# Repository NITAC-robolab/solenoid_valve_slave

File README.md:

# 概要
電磁弁を制御するためのスレーブ．

<br>
<br>

# リポジトリ構成
```tree
├── circuit --> 回路図，基板データ
└── program --> プログラム
```

<br>
<br>

# 動作確認環境
- IDE : MPLAB X IDE v4.15
- コンパイラ : XC16 v1.41
- コンパイルオプション : -std=c99
    - File -> Project Properties -> Categories: -> Conf: [default] -> XC16(Global Options) -> xc16-gcc -> Additional options: で指定

<br>
<br>

# 通信データ ( M->S )

| byte | 内容 |
|:-:|:--|
| 1 | ON / OFF ( 1ch ~ 8ch )|
| 2 | ON / OFF ( 9ch ~ 16ch )|

<br>
<br>

# 使用している周辺モジュール

* UART1(RX) ：Raspberry Pi との通信

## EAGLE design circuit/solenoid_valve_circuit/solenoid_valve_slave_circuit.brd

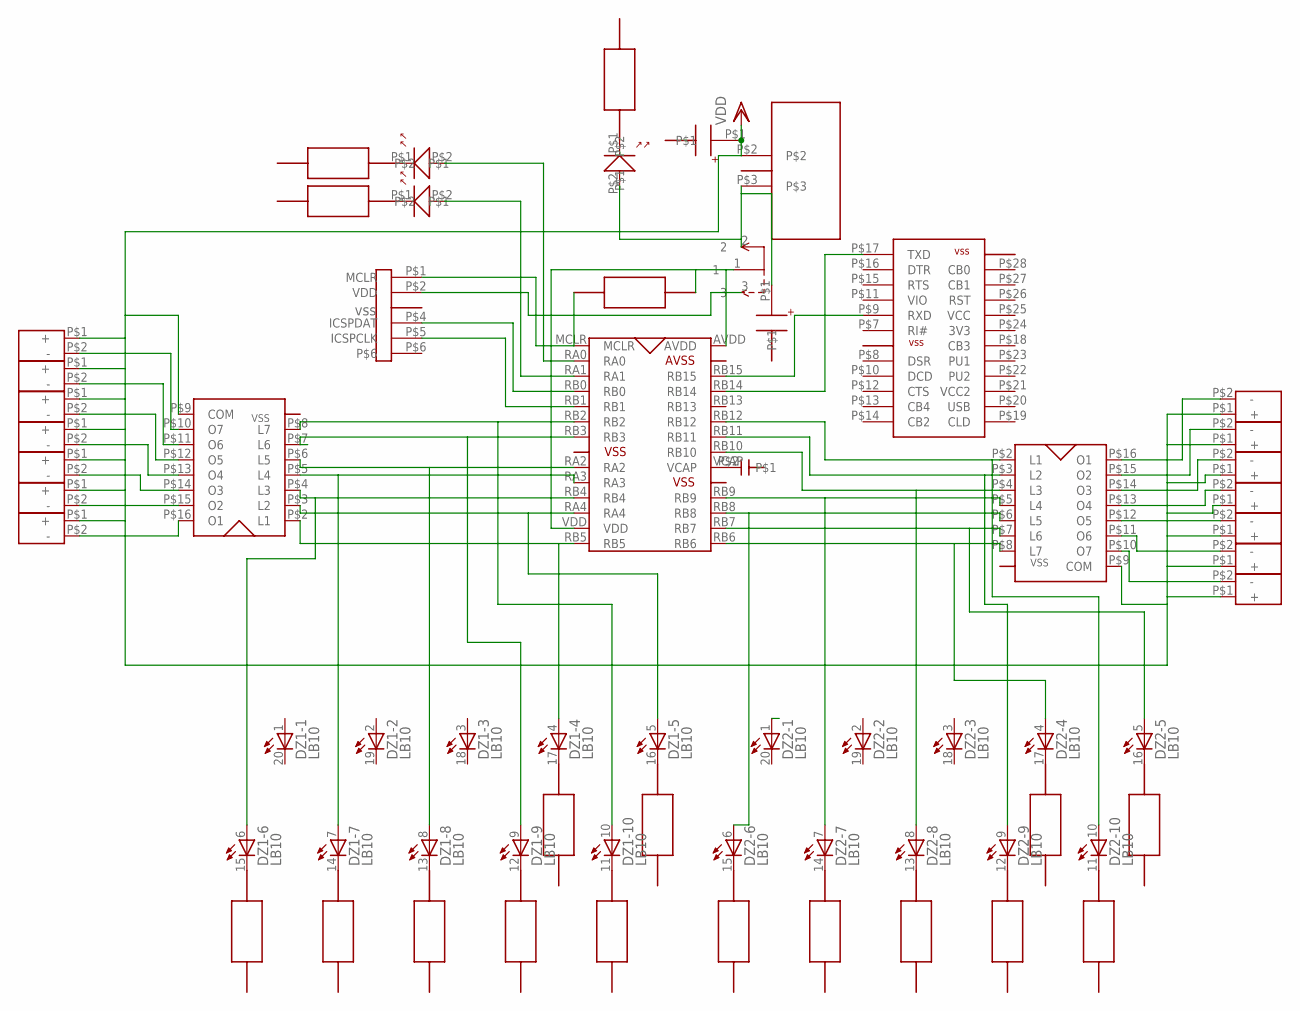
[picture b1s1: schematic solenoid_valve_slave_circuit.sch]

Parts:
DSPIC33FJ128MC1: DSPIC33FJ128MC; PIC_28P_2
DZ1, DZ2: LB10
SLIDE_SWITCH1: SLIDE_SWITCH_3
U$1, U$41: CAPACITOR_33
U$2, U$6, U$7, U$13, U$14, U$15, U$16, U$17, U$18, U$19, U$20, U$21, U$22, U$23, U$24, U$25, U$26, U$43: CHIP_RESISTOR
U$3: WRITER
U$4, U$5, U$42: LED
U$8, U$10: TRANSISTOR_TBD62003APG
U$9: REGULATOR
U$11: CAPACITORS_106
U$12: SERIALCOM
U$27, U$28, U$29, U$30, U$31, U$32, U$33, U$34, U$35, U$36, U$37, U$38, U$39, U$40: XHCONNECTOR_2PIN

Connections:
unnamed: SLIDE_SWITCH1.2, U$9.P$3, U$41.P$1, U$42.P$2
unnamed: DSPIC33FJ128MC1.AVDD, DSPIC33FJ128MC1.VDD, SLIDE_SWITCH1.1
unnamed: SLIDE_SWITCH1.3, U$3.P$2 (VDD)
unnamed: DSPIC33FJ128MC1.MCLR, U$3.P$1 (MCLR)
unnamed: DSPIC33FJ128MC1.RB0, U$3.P$4 (ICSPDAT)
unnamed: DSPIC33FJ128MC1.RB1, U$3.P$5 (ICSPCLK)
unnamed: DSPIC33FJ128MC1.RA0, U$4.P$2
unnamed: DSPIC33FJ128MC1.RA1, U$5.P$2
unnamed: DSPIC33FJ128MC1.RB2, DZ1.10 (A), U$8.P$8 (L7)
unnamed: DSPIC33FJ128MC1.RA3, DZ1.7 (A), U$8.P$5 (L4)
unnamed: DSPIC33FJ128MC1.RA2, DZ1.8 (A), U$8.P$6 (L5)
unnamed: DSPIC33FJ128MC1.RB3, DZ1.9 (A), U$8.P$7 (L6)
unnamed: DSPIC33FJ128MC1.RA4, DZ1.5 (A), U$8.P$3 (L2)
unnamed: DSPIC33FJ128MC1.RB5, DZ1.4 (A), U$8.P$2 (L1)
unnamed: DSPIC33FJ128MC1.RB6, DZ2.4 (A), U$10.P$8 (L7)
unnamed: DSPIC33FJ128MC1.RB7, DZ2.5 (A), U$10.P$7 (L6)
unnamed: DSPIC33FJ128MC1.RB10, DZ2.8 (A), U$10.P$4 (L3)
unnamed: DSPIC33FJ128MC1.RB11, DZ2.9 (A), U$10.P$3 (L2)
unnamed: DSPIC33FJ128MC1.RB12, DZ2.10 (A), U$10.P$2 (L1)
unnamed: DSPIC33FJ128MC1.VCAP, U$11.P$2
unnamed: DSPIC33FJ128MC1.RB15, U$12.P$9 (RXD)
unnamed: DSPIC33FJ128MC1.RB14, U$12.P$17 (TXD)
unnamed: U$10.P$10 (O7), U$38.P$2 (-)
unnamed: U$10.P$11 (O6), U$37.P$2 (-)
unnamed: U$10.P$12 (O5), U$36.P$2 (-)
unnamed: U$10.P$13 (O4), U$35.P$2 (-)
unnamed: U$8.P$10 (O7), U$33.P$2 (-)
unnamed: U$8.P$11 (O6), U$32.P$2 (-)
unnamed: U$8.P$12 (O5), U$31.P$2 (-)
unnamed: U$8.P$13 (O4), U$30.P$2 (-)
unnamed: U$8.P$14 (O3), U$29.P$2 (-)
unnamed: U$8.P$15 (O2), U$28.P$2 (-)
unnamed: U$8.P$16 (O1), U$27.P$2 (-)
unnamed: U$10.P$14 (O3), U$34.P$2 (-)
unnamed: U$10.P$15 (O2), U$39.P$2 (-)
unnamed: U$10.P$16 (O1), U$40.P$2 (-)
unnamed: DSPIC33FJ128MC1.RB9, DZ2.7 (A), U$10.P$5 (L4)
unnamed: DSPIC33FJ128MC1.RB8, DZ2.6 (A), U$10.P$6 (L5)
unnamed: DSPIC33FJ128MC1.RB4, DZ1.6 (A), U$8.P$4 (L3)
VDD: U$1.P$1, U$8.P$9 (COM), U$9.P$2, U$10.P$9 (COM), U$27.P$1 (+), U$28.P$1 (+), U$29.P$1 (+), U$30.P$1 (+), U$31.P$1 (+), U$32.P$1 (+), U$33.P$1 (+), U$34.P$1 (+), U$35.P$1 (+), U$36.P$1 (+), U$37.P$1 (+), U$38.P$1 (+), U$39.P$1 (+), U$40.P$1 (+)

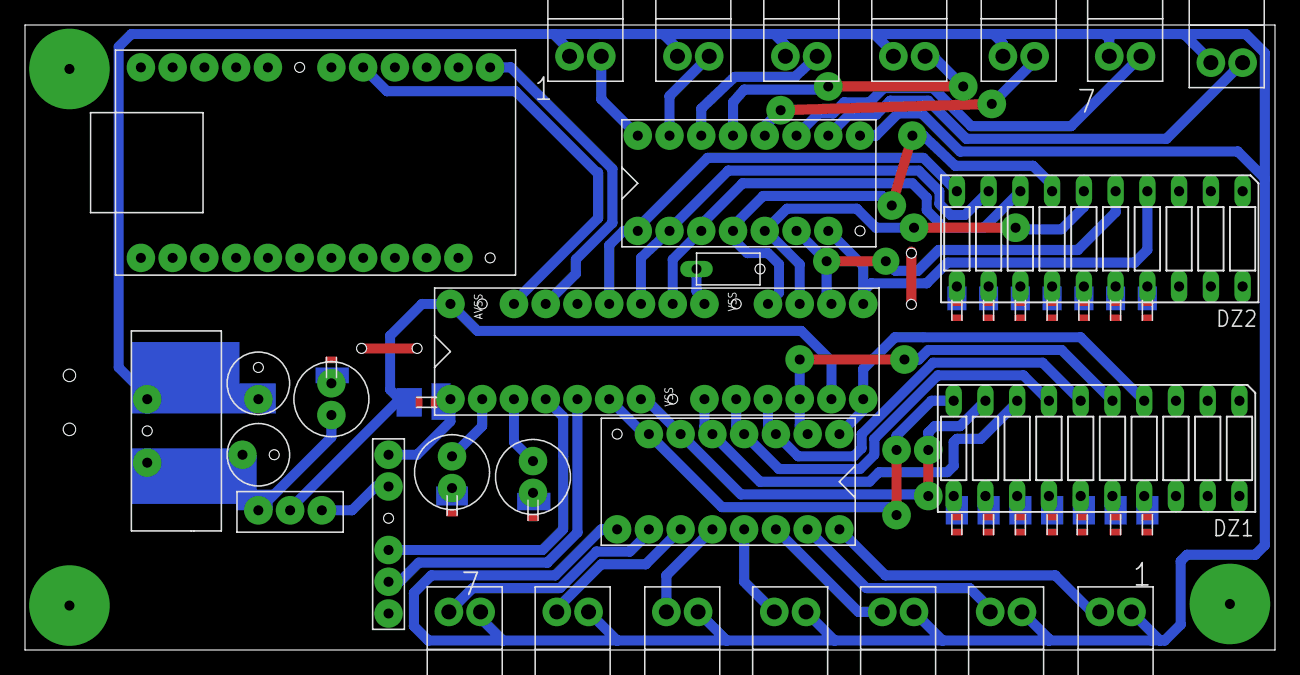
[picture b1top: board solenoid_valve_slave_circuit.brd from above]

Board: 2 copper layers, 100.0 x 50.0 mm, 47 parts (0 on the bottom side), 40 nets.

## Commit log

2020-01-14 pwm_control からプログラムをコピーしてきた．
    ◍ 通信ができることを確認．
2020-03-01 動作確認完了
    commit 5ceaa4b08a21eab67eb7516fd90b9855c94893c7
    Author: Takuto Jibiki <eipuuuuk825@gmail.com>
    Date: Sun Mar 1 12:11:20 2020 +0900
    [地引] README を追加
    commit 90dbaa48f151ba28be088cb7c352ae35e69c4bc8
    Author: Takuto Jibiki <eipuuuuk825@gmail.com>
2020-08-19 eagleの基板データを追加
    eagleの基板データを修正
    ・コネクタの間隔をあけた
    ・それに伴うパターンの変更
    ・出力データの削除
